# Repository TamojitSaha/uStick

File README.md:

# uStick
μStick (pronounced as "mu stick")or uStick is a 32bit Arm Cortex M0+ based Arduino Compatible micro development board specially designed for battery driven projects/products.
The project is available to order from [OSH Park](https://oshpark.com/projects/SfXMe0NL).

## Features:
- Micro Dev Board (39mm x 15mm)
- ATSAMD11C14 -- 32bit Arm Cortex M0+ 
- 16kb flash, 4kb SRAM
- Battery charging modes(user configurable): 
	- 1. USB 100mA
	- 2. USB 500mA
	- 3. Resistor settable charging current upto 1.6A
- Low noise LDO
  - low Output-VoltageNoise:12 μVRMSTypical
  - PSRRat 1 kHz:75 dB Typical
  - OutputVoltageTolerance(VOUT≥3.3 V): ±2%
  - Low IQ(Enabled,No Load):30 μA Typical
  - Low Dropout(VOUT≥3.3 V): 95 mV Typical at 500 mA Load
- Choosable EEPROM(16-512 MegaBit, refer to [this](https://github.com/Marzogh/SPIMemory) library)
- Auto charging and system power management
- Charging status and power good indicator
- Button configurable for reset or general use (pin D15) with debouncing.
  -  Use as reset (default), with bootloader entry via reset double-tap
  - Use as a general purpose button, with bootloader entry by holding during powerup.
- ESD protection on USB D+ and D- lines
- 9 solder jumpers on PCB bottom for configuration flexibility
- Arduino compatible (use the Arduino IDE to upload)

## Design Layout

&nbsp;&nbsp;

## License
The source files are released under [CC-BY-SA 4.0](https://creativecommons.org/licenses/by-sa/4.0/).

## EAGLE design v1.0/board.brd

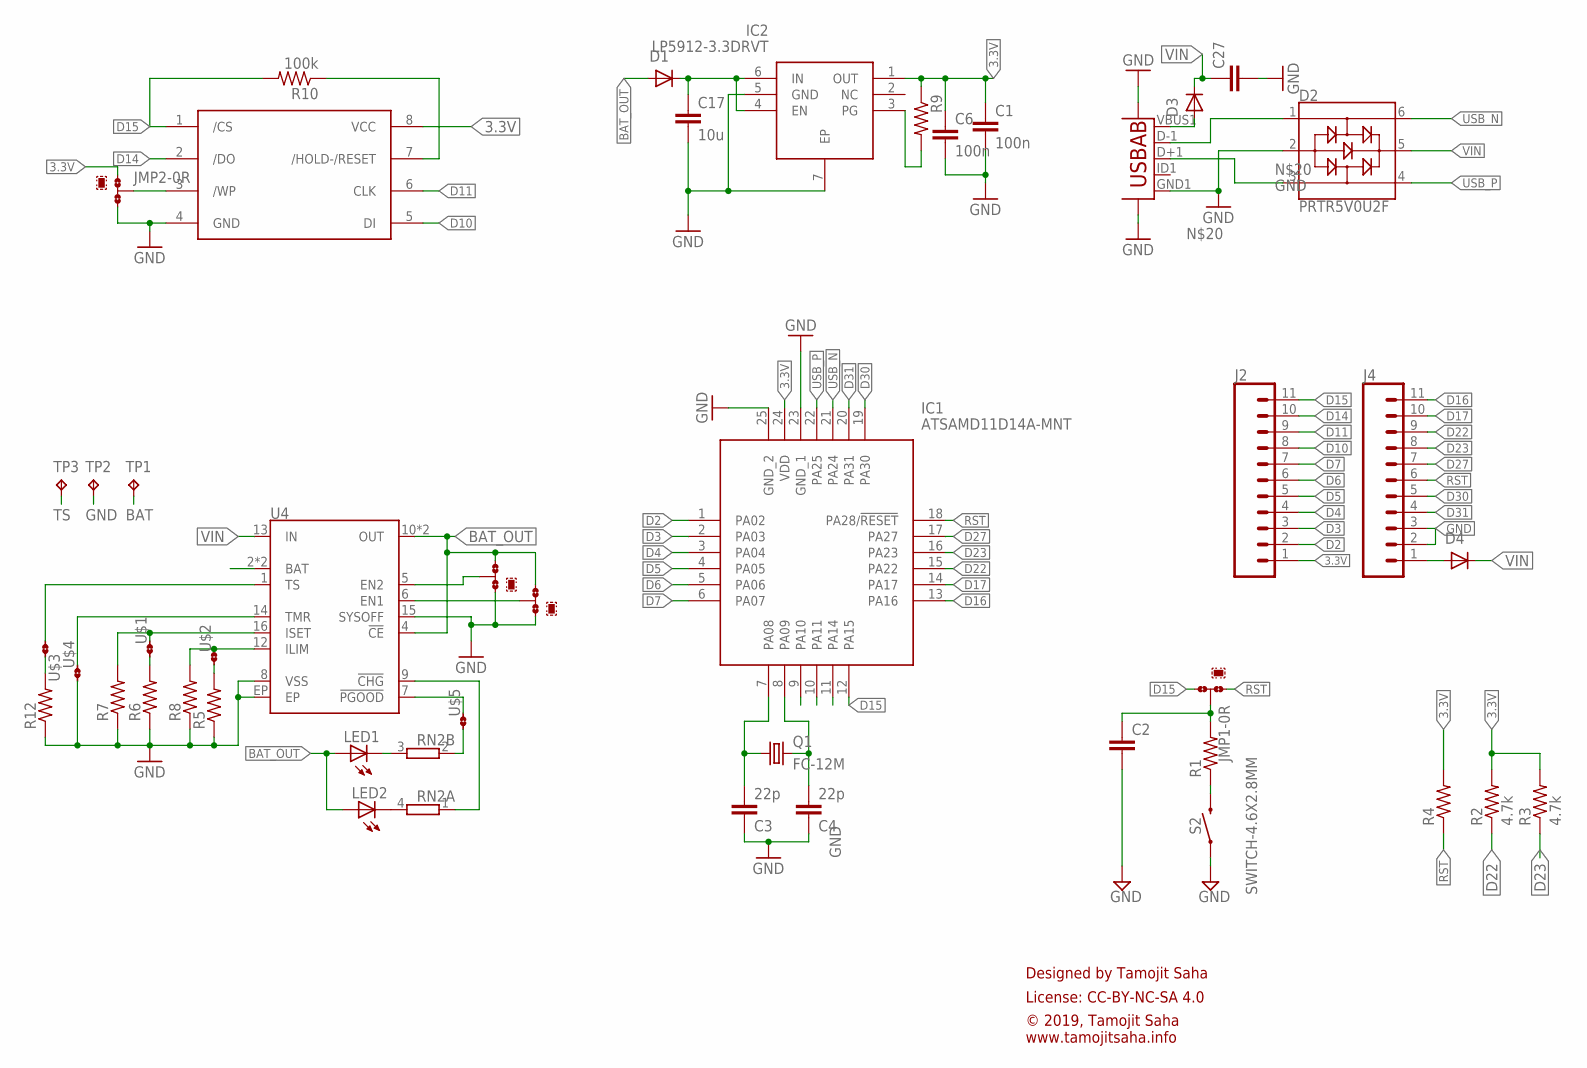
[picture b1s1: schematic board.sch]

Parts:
C1, C6: 100n; C0402
C2: C-EUC0402; C0402
C3, C4: 22p; C0402
C17: 10u; C0603
C27: C-EUC0603; C0603
D1, D3, D4: PMEG1030; SOD323(F)
D2: PRTR5V0U2F; SOT886
EEPROM1: W25Q128JVPIQ; SON127P600X500X80-9N
IC1: ATSAMD11D14A-MNT; QFN50P400X400X90-25N
IC2: LP5912-3.3DRVT; WSON-6
J2, J4: CONN_111X11_NO_SILK; 1X11_NO_SILK
JMP1, JMP2, JMP3, JMP4: 0R-JUMPA; A0R-JMP
LED1, LED2: LED_ESML0603; LED_SML0603
Q1: FC-12M
R1, R4, R5, R6, R7, R8, R9, R12: R-US_R0402; R0402
R2, R3: 4.7k; R0402
R10: 100k; R0402
RN2: 2R-NEXB24V; EXB24V
S2: SWITCH-4.6X2.8MM; TACTILE_SWITCH_SMD_4.6X2.8MM
TP1, TP2, TP3: TPB1,27; B1,27
U3: USB""; USB-MICRO-SMD
U4: BQ24075; PVQFN-N16
U$1, U$2, U$3, U$4, U$5: JMP-2-NO-0402

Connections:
3.3V: C1.1, C6.1, EEPROM1.8 (VCC), IC1.24 (VDD), IC2.1 (OUT), J2.1, JMP2.1, R2.2, R3.2, R4.2, R9.1
BAT: TP1.TP, U4.2 (BAT), U4.3 (BAT)
BAT_OUT: D1.2 (A), JMP3.3, JMP4.3, LED1.A, LED2.A, U4.4 (!CE!), U4.10 (OUT), U4.11 (OUT)
D2: IC1.1 (PA02), J2.2
D3: IC1.2 (PA03), J2.3
D4: IC1.3 (PA04), J2.4
D5: IC1.4 (PA05), J2.5
D6: IC1.5 (PA06), J2.6
D7: IC1.6 (PA07), J2.7
D10: EEPROM1.5 (DI), IC1.9 (PA10), J2.8
D11: EEPROM1.6 (CLK), IC1.10 (PA11), J2.9
D14: EEPROM1.2 (/DO), IC1.11 (PA14), J2.10
D15: EEPROM1.1 (/CS), IC1.12 (PA15), J2.11, JMP1.3, R10.2
D16: IC1.13 (PA16), J4.11
D17: IC1.14 (PA17), J4.10
D22: IC1.15 (PA22), J4.9, R2.1
D23: IC1.16 (PA23), J4.8, R3.1
D27: IC1.17 (PA27), J4.7
D30: IC1.19 (PA30), J4.5
D31: IC1.20 (PA31), J4.4
GND: C1.2, C2.2, C3.1, C4.1, C6.2, C17.2, C27.2, D2.2, EEPROM1.4 (GND), IC1.23 (GND_1), IC1.25 (GND_2), IC2.5 (GND), IC2.7 (EP), J4.2, J4.3, JMP2.3, JMP3.1, JMP4.1, R5.1, R6.1, R7.1, R8.1, R12.1, S2.1, S2.2 (1), TP2.TP, U3.GND1 (GND), U3.SH1, U3.SH2, U4.8 (VSS), U4.15 (SYSOFF), U4.EP, U$4.1
unnamed: LED1.C, RN2.3 (2)
unnamed: C3.2, IC1.7 (PA08), Q1.1
unnamed: D2.1, U3.D-1 (D-)
unnamed: D2.3, U3.D+1 (D+)
unnamed: R6.2, U$1.1
unnamed: R7.2, U4.16 (ISET), U$1.2
unnamed: C4.2, IC1.8 (PA09), Q1.2
unnamed: C2.1, JMP1.2, R1.2
unnamed: R12.2, U$3.2
unnamed: R5.2, U$2.1
unnamed: R8.2, U4.12 (ILIM), U$2.2
unnamed: U4.14 (TMR), U$4.2
unnamed: C17.1, D1.1 (K), IC2.4 (EN), IC2.6 (IN)
unnamed: JMP4.2, U4.5 (EN2)
unnamed: RN2.2 (1), U$5.1
unnamed: LED2.C, RN2.4 (2)
unnamed: JMP3.2, U4.6 (EN1)
unnamed: RN2.1, U4.9 (!CHG!)
unnamed: U4.7 (!PGOOD!), U$5.2
unnamed: D3.2 (A), U3.VBUS1 (VBUS)
unnamed: D4.2 (A), J4.1
unnamed: IC2.3 (PG), R9.2
unnamed: EEPROM1.3 (/WP), JMP2.2
unnamed: EEPROM1.7 (/HOLD-/RESET), R10.1
unnamed: R1.1, S2.3 (2), S2.4 (2)
RST: IC1.18 (PA28/!RESET), J4.6, JMP1.1, R4.1
TS: TP3.TP, U4.1 (TS), U$3.1
USB_N: D2.6, IC1.21 (PA24)
USB_P: D2.4, IC1.22 (PA25)
VIN: C27.1, D2.5, D3.1 (K), D4.1 (K), U4.13 (IN)

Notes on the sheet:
Designed by Tamojit Saha
License: CC-BY-NC-SA 4.0
© 2019, Tamojit Saha www.tamojitsaha.info

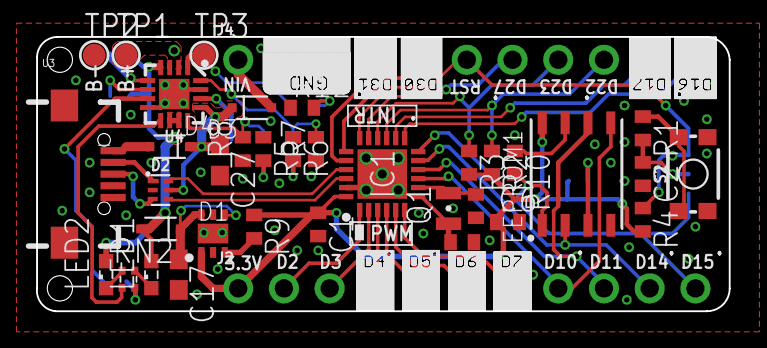
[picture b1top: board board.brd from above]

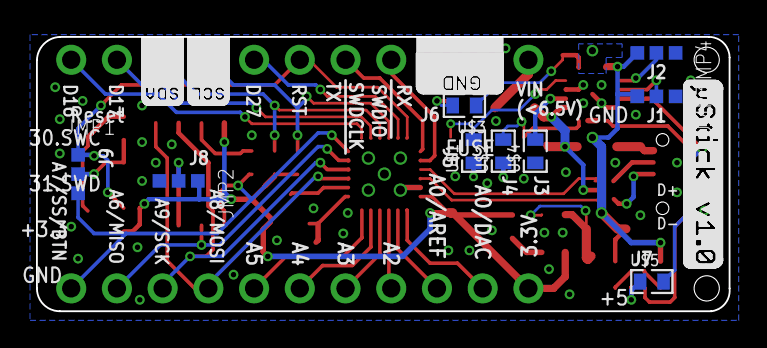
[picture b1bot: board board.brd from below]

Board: 2 copper layers, 38.5 x 15.2 mm, 46 parts (9 on the bottom side), 51 nets.

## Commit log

2019-03-02 added EagleCAD files

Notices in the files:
parts and their libraries:
SparkFun-IC-Power: Licensing: Creative Commons ShareAlike 4.0 International - https://creativecommons.org/licenses/by-sa/4.0
PatternAgents-ProtoPads: License : http://creativecommons.org/licenses/by-sa/4.0
(Creative Commons 4.0)
